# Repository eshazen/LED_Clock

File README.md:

# LED Clock

Yet another LED pseudo-analog clock.
<br>6 concentric circles of 60 LEDs plus one of 12 LEDs.
<br>Arduino Nano ESP32.

Current code (`clock_v3`) runs on 1Hz interrupts but expects
periodic time updates of the format `[hh:mm:ss]` at 1200 baud
from an external RTC.

First release code (`clock_v2`) just uses 1Hz timer interrupts
and provides hour / minute set buttons.

No ECOs on the PC board.  Forgot mounting holes though.
See `Case` folder for a two-part 3D printed wall hangar
with a little control panel for the set buttons.

Works OK but loses ~1min/day.  Need to work on the timekeeping.

### 2026-04-19

Implemented initial RTC board software.

### 2026-04-12

Working on SimpleRTC add-on to keep better time.
<br>Need a serial port on the ESP32.
<br>It's confusing:
https://forum.arduino.cc/t/nano-esp32-onboard-uart-and-pin-numbering-issues/1269099/9

I _think_ this should work:

    Serial1.begin(1200, SERIAL_8N1, D11, D12);

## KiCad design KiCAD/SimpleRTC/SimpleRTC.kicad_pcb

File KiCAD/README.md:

# PCB designs

`Led_clock_sector` is the main PCB.  No errors I'm aware of.
The current version here has mounting holes which are missing
from the V1 as-built version.

`SimpleRTC` is a small board with RTC, MCU and pushbuttons.
The version here in git as of this writing is incomplete...
no doubt there is an un-committed update on a laptop somewhere.

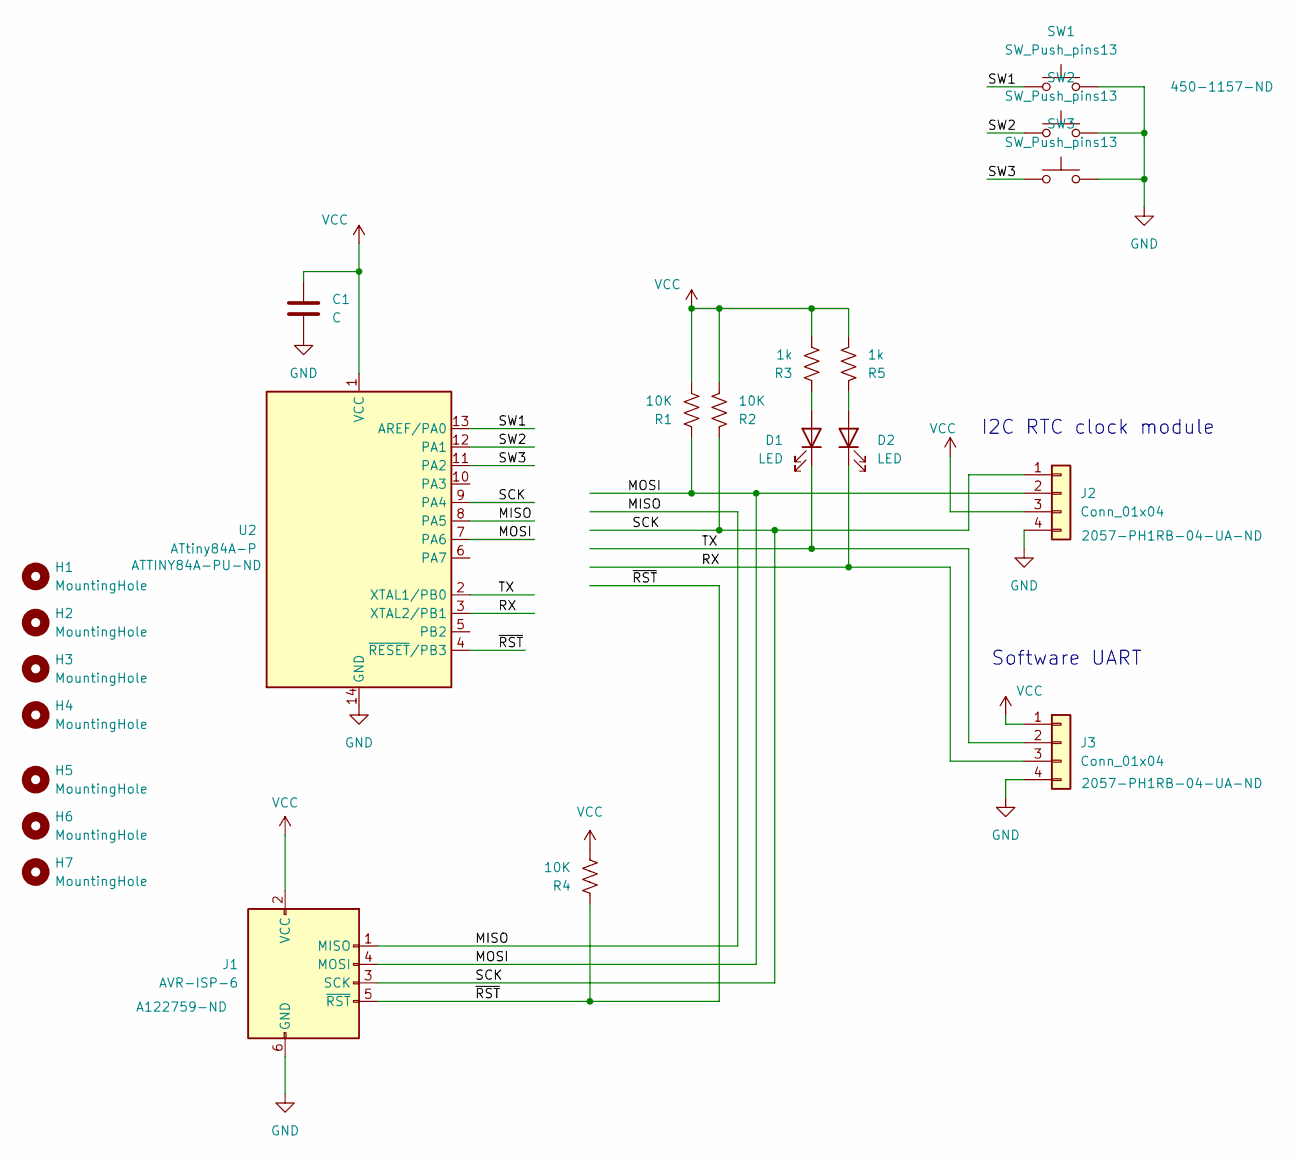
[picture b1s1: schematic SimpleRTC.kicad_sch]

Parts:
C1: C; C_1206_3216Metric_Pad1.33x1.80mm_HandSolder
D1, D2: LED; LED_1206_3216Metric_Pad1.42x1.75mm_HandSolder
H1, H2, H3, H4, H5, H6, H7: MountingHole; mtg_hole_256
J1: AVR-ISP-6; IDC-Header_2x03_P2.54mm_Vertical
J2: Conn_01x04; RTC_module
J3: Conn_01x04; PinHeader_1x04_P2.54mm_Horizontal
R1, R2, R4: 10K; R_1206_3216Metric_Pad1.30x1.75mm_HandSolder; DIGIKEY CF14JT10K0CT-ND
R3, R5: 1k; R_1206_3216Metric_Pad1.30x1.75mm_HandSolder; DIGIKEY CF14JT10K0CT-ND
SW1, SW2, SW3: SW_Push_pins13; SW_1437565-3
U2: ATtiny84A-P; DIP-14_W7.62mm

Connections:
/MISO: J1.1 (MISO), U2.8 (PA5)
/MOSI: J1.4 (MOSI), J2.2, R1.1, U2.7 (PA6)
/RX: D2.1 (K), J3.3, U2.3 (XTAL2/PB1)
/SCK: J1.3 (SCK), J2.1, R2.1, U2.9 (PA4)
/SW1: SW1.1, U2.13 (AREF/PA0)
/SW2: SW2.1, U2.12 (PA1)
/SW3: SW3.1, U2.11 (PA2)
/TX: D1.1 (K), J3.2, U2.2 (XTAL1/PB0)
/~RST: J1.5 (~RST), R4.1, U2.4 (~RESET/PB3)
GND: C1.2, J1.6 (GND), J2.4, J3.4, SW1.3, SW2.3, SW3.3, U2.14 (GND)
unnamed: D1.2 (A), R3.1
unnamed: D2.2 (A), R5.1
VCC: C1.1, J1.2 (VCC), J2.3, J3.1, R1.2, R2.2, R3.2, R4.2, R5.2, U2.1 (VCC)

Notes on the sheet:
I2C RTC clock module
Software UART

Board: 2 copper layers, 22 parts (14 on the bottom side), 13 nets, no tracks yet.

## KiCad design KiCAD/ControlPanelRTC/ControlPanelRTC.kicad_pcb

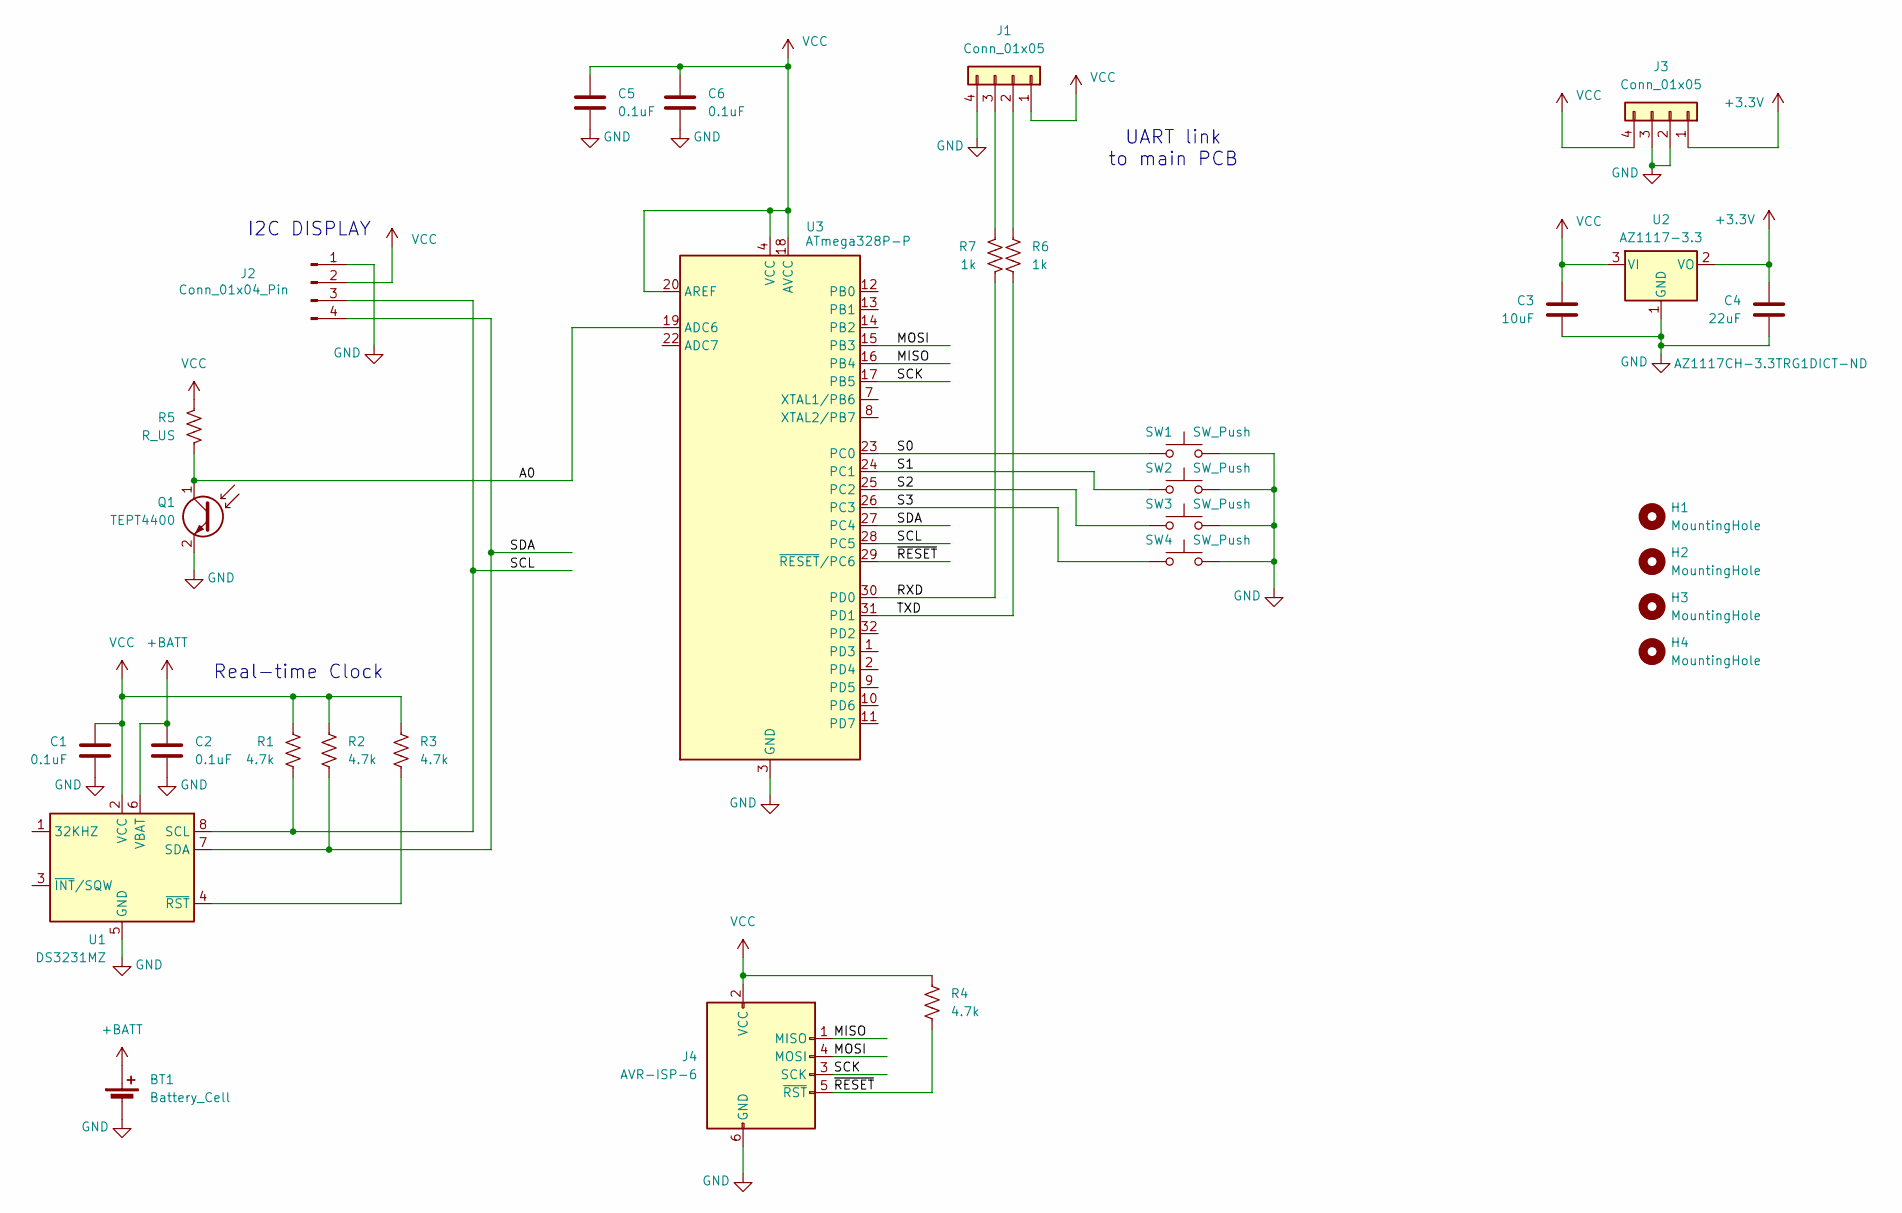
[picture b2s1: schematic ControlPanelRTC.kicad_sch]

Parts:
BT1: Battery_Cell; BatteryHolder_Keystone_3000_1x12mm
C1, C2, C5, C6: 0.1uF; C_1206_3216Metric_Pad1.33x1.80mm_HandSolder
C3: 10uF; C_1206_3216Metric_Pad1.33x1.80mm_HandSolder
C4: 22uF; C_1206_3216Metric_Pad1.33x1.80mm_HandSolder
H1, H2, H3, H4: MountingHole; mtg_440
J1, J3: Conn_01x05; PinHeader_1x04_P2.54mm_Horizontal
J2: Conn_01x04_Pin; OLED_0.96IN
J4: AVR-ISP-6; PinHeader_2x03_P2.54mm_Horizontal
Q1: TEPT4400; LED_D3.0mm_Clear
R1, R2, R3, R4: 4.7k; R_1206_3216Metric
R5: R_US; R_1206_3216Metric
R6, R7: 1k; R_1206_3216Metric
SW1, SW2, SW3, SW4: SW_Push; SW4_1825910-B_TEC
U1: DS3231MZ; SOIC-8_3.9x4.9mm_P1.27mm
U2: AZ1117-3.3; SOT-223-3_TabPin2
U3: ATmega328P-P; TQFP-32_7x7mm_P0.8mm

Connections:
+3.3V: C4.1, J3.1, U2.2 (VO)
+BATT: BT1.1 (+), C2.1, U1.6 (VBAT)
/A0: Q1.1 (C), R5.2, U3.19 (ADC6)
/MISO: J4.1 (MISO), U3.16 (PB4)
/MOSI: J4.4 (MOSI), U3.15 (PB3)
/RXD: R7.2, U3.30 (PD0)
/S0: SW1.1, U3.23 (PC0)
/S1: SW2.1, U3.24 (PC1)
/S2: SW3.1, U3.25 (PC2)
/S3: SW4.1, U3.26 (PC3)
/SCK: J4.3 (SCK), U3.17 (PB5)
/SCL: J2.3, R1.2, U1.8 (SCL), U3.28 (PC5)
/SDA: J2.4, R2.2, U1.7 (SDA), U3.27 (PC4)
/TXD: R6.2, U3.31 (PD1)
/~RESET: J4.5 (~RST), R4.2, U3.29 (~RESET/PC6)
GND: BT1.2 (-), C1.2, C2.2, C3.2, C4.2, C5.2, C6.2, J1.4, J2.1, J3.2, J3.3, J4.6 (GND), Q1.2 (E), SW1.3, SW2.3, SW3.3, SW4.3, U1.5 (GND), U2.1 (GND), U3.3 (GND), U3.5 (GND), U3.21 (GND)
unnamed: J1.2, R6.1
unnamed: J1.3, R7.1
unnamed: R3.2, U1.4 (~RST)
VCC: C1.1, C3.1, C5.1, C6.1, J1.1, J2.2, J3.4, J4.2 (VCC), R1.1, R2.1, R3.1, R4.1, R5.1, U1.2 (VCC), U2.3 (VI), U3.4 (VCC), U3.6 (VCC), U3.18 (AVCC), U3.20 (AREF)

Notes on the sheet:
UART link to main PCB
I2C DISPLAY
Real-time Clock

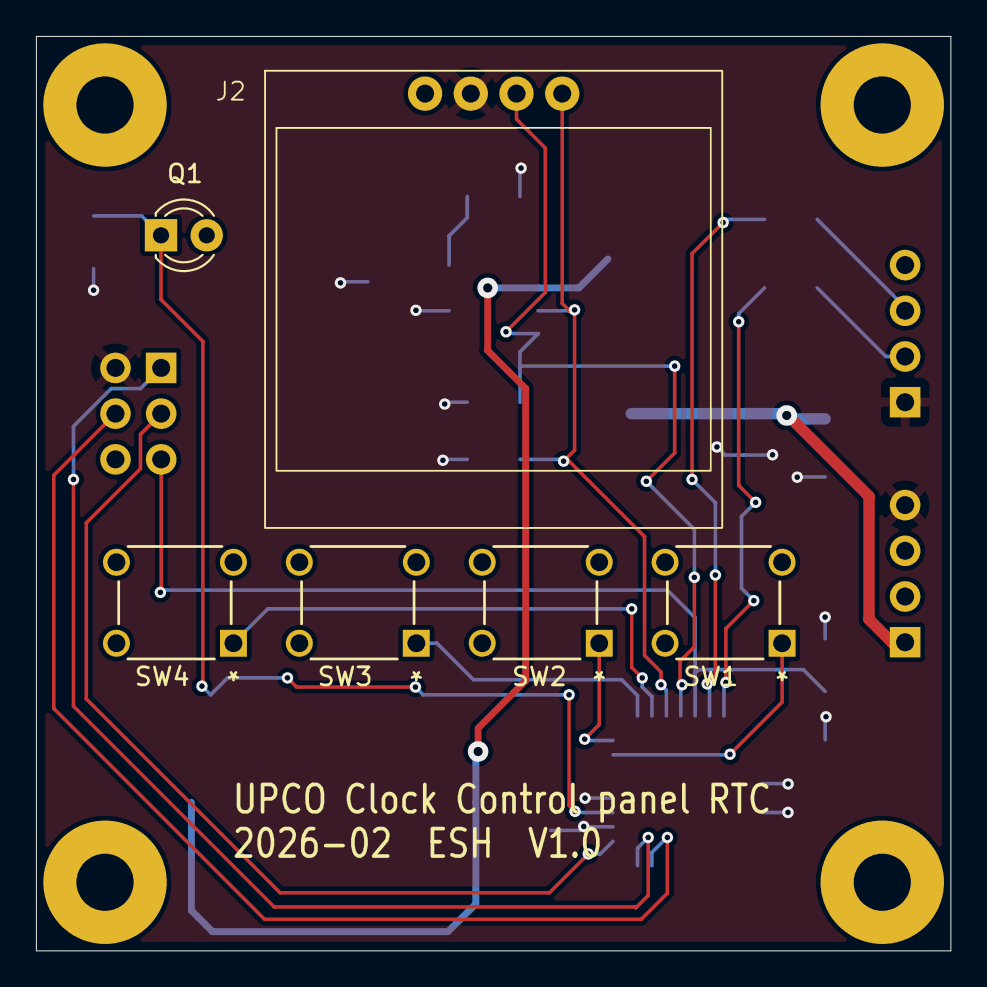
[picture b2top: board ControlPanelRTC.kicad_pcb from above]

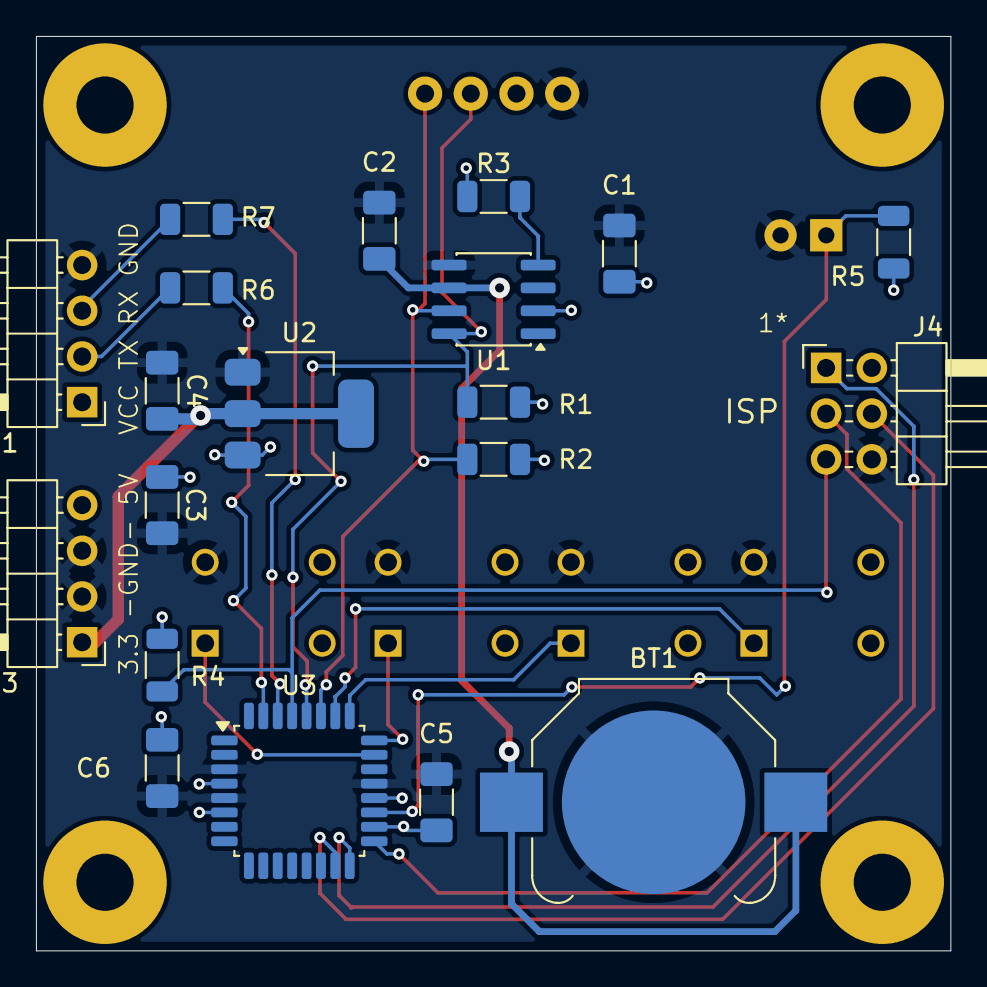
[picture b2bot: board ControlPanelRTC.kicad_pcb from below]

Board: 2 copper layers, 50.8 x 50.8 mm, 30 parts (20 on the bottom side), 20 nets.

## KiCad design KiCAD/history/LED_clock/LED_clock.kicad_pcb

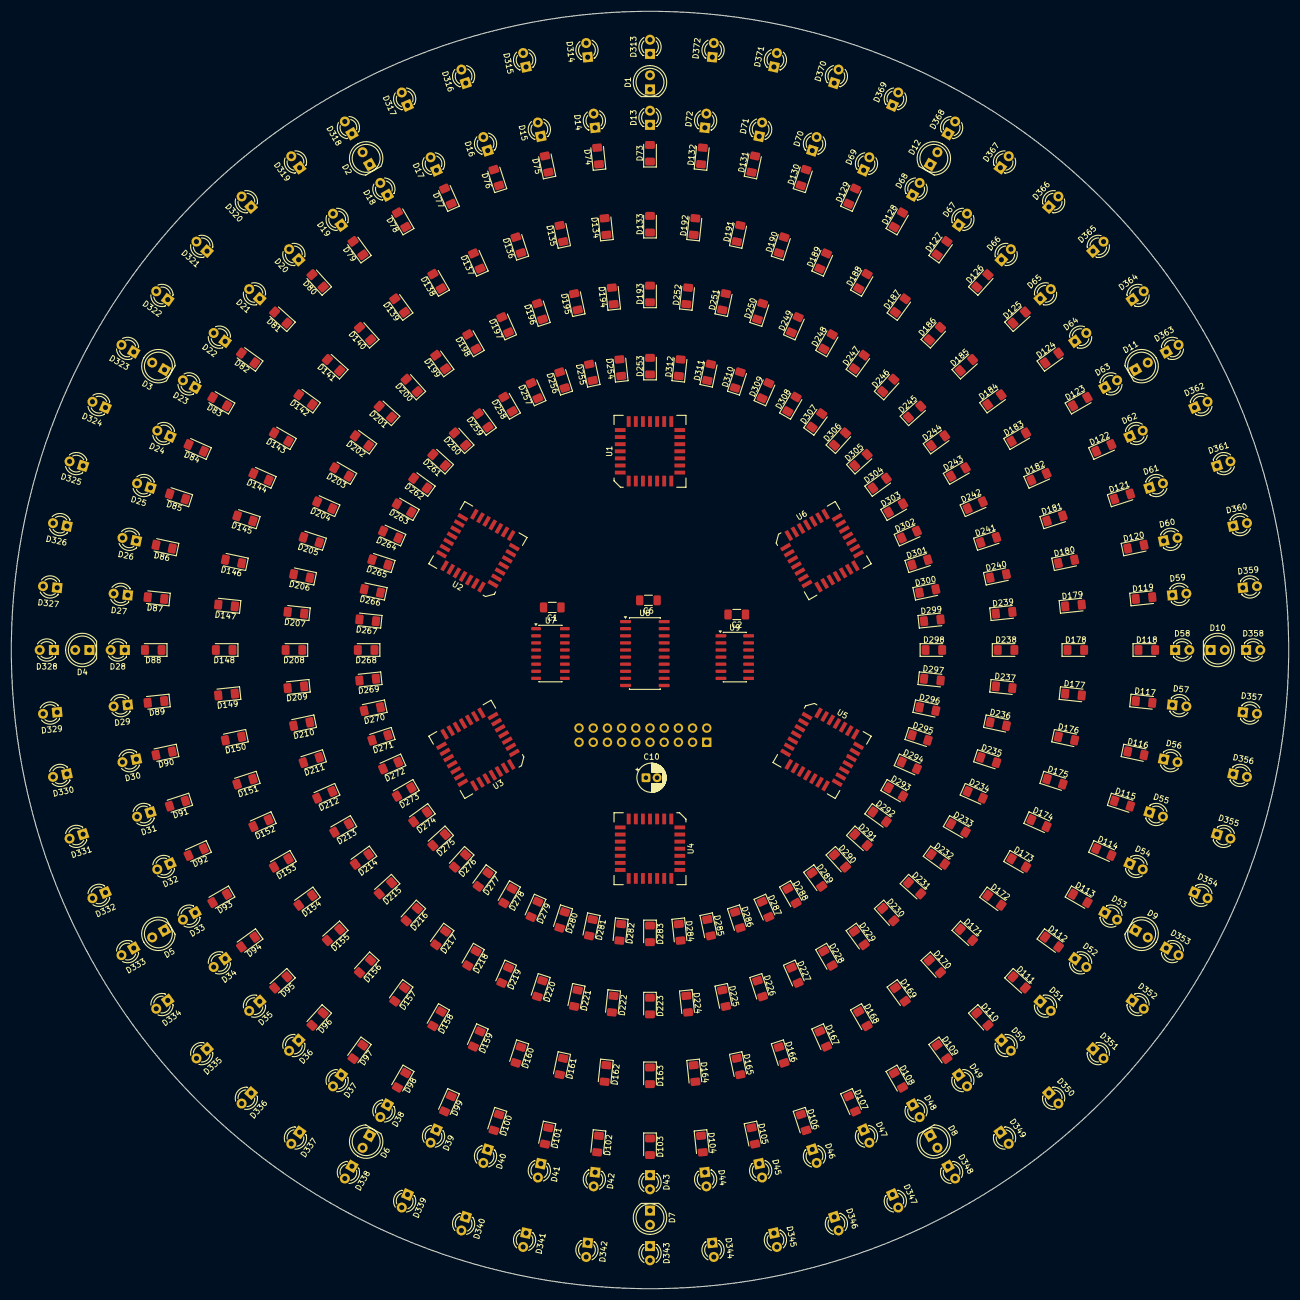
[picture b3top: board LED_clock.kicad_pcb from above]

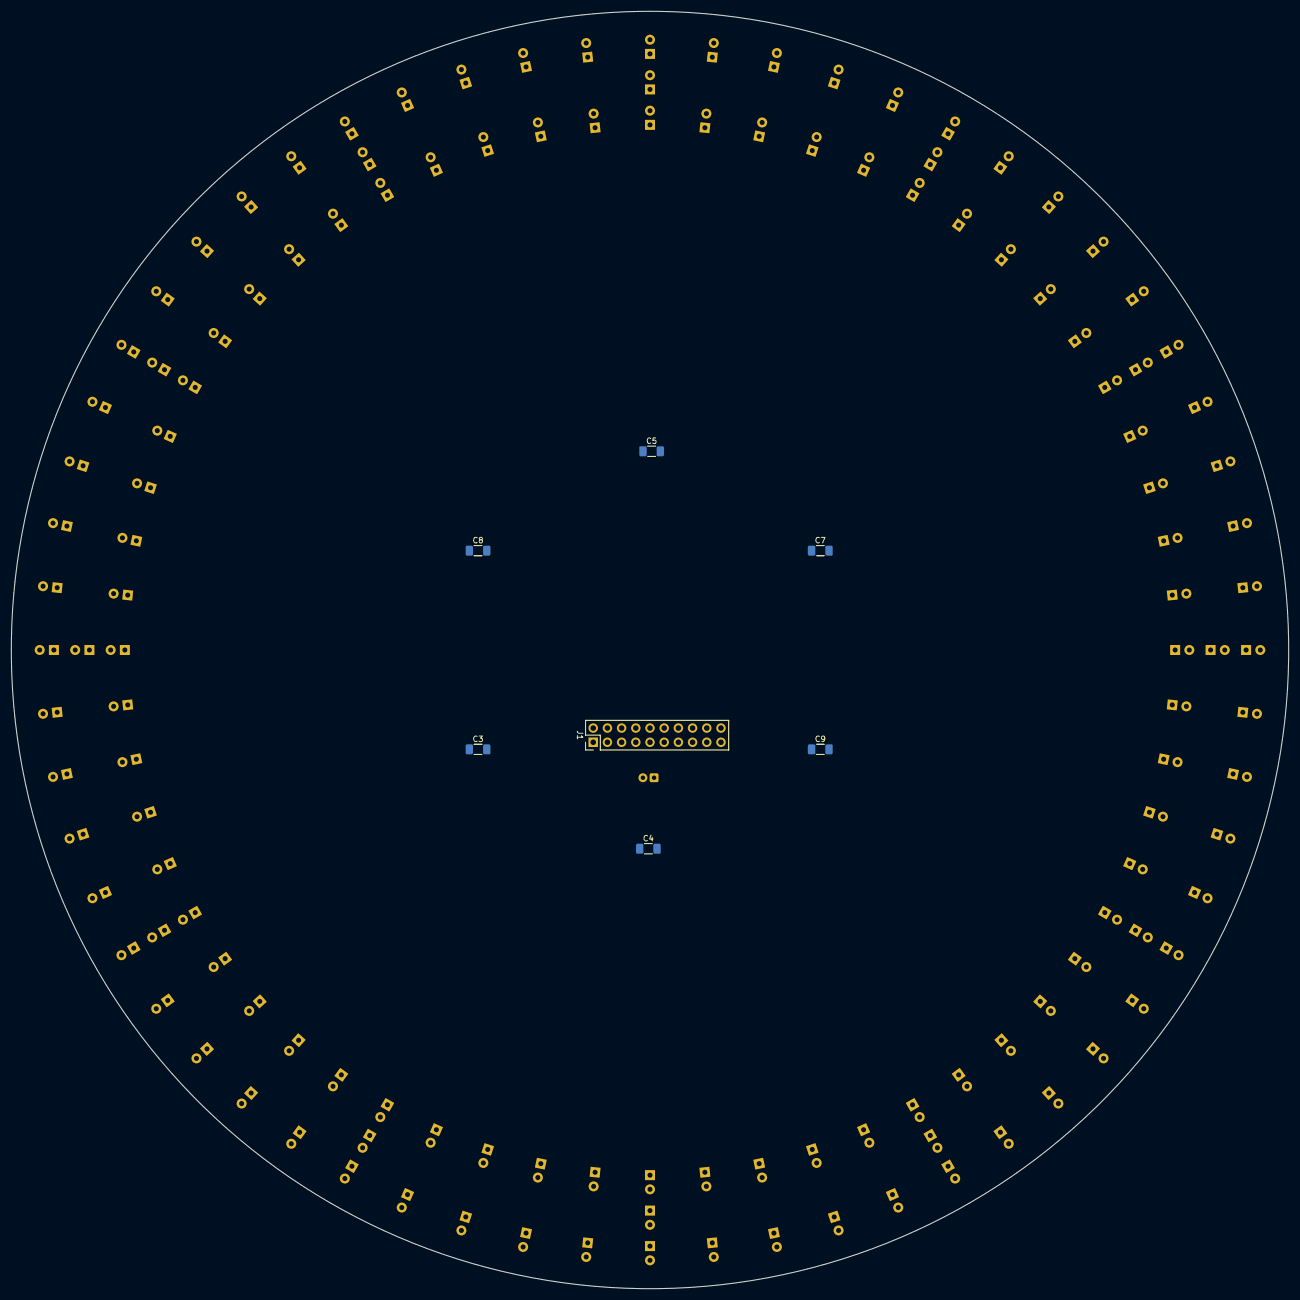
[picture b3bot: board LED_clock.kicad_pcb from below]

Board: 4 copper layers, 228.6 x 228.6 mm, 392 parts (7 on the bottom side), 121 nets, no tracks yet.

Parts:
C1, C2, C3, C4, C5, C6, C7, C8, C9: 0.1uF; C_1206_3216Metric_Pad1.33x1.80mm_HandSolder
C10: 33uF; CP_Radial_D5.0mm_P2.00mm
D1, D2, D3, D4, D5, D6, D7, D8, D9, D10, D11, D12: LED; LED_D5.0mm
D13, D14, D15, D16, D17, D18, D19, D20, D21, D22, D23, D24, D25, D26, D27, D28, D29, D30, D31, D32, D33, D34, D35, D36, D37, D38, D39, D40, D41, D42, D43, D44, D45, D46, D47, D48, D49, D50, D51, D52, D53, D54, D55, D56, D57, D58, D59, D60, D61, D62, D63, D64, D65, D66, D67, D68, D69, D70, D71, D72, D313, D314, D315, D316, D317, D318, D319, D320, D321, D322, D323, D324, D325, D326, D327, D328, D329, D330, D331, D332, D333, D334, D335, D336, D337, D338, D339, D340, D341, D342, D343, D344, D345, D346, D347, D348, D349, D350, D351, D352, D353, D354, D355, D356, D357, D358, D359, D360, D361, D362, D363, D364, D365, D366, D367, D368, D369, D370, D371, D372: LED; LED_D3.0mm
D73, D74, D75, D76, D77, D78, D79, D80, D81, D82, D83, D84, D85, D86, D87, D88, D89, D90, D91, D92, D93, D94, D95, D96, D97, D98, D99, D100, D101, D102, D103, D104, D105, D106, D107, D108, D109, D110, D111, D112, D113, D114, D115, D116, D117, D118, D119, D120, D121, D122, D123, D124, D125, D126, D127, D128, D129, D130, D131, D132, D133, D134, D135, D136, D137, D138, D139, D140, D141, D142, D143, D144, D145, D146, D147, D148, D149, D150, D151, D152, D153, D154, D155, D156, D157, D158, D159, D160, D161, D162, D163, D164, D165, D166, D167, D168, D169, D170, D171, D172, D173, D174, D175, D176, D177, D178, D179, D180, D181, D182, D183, D184, D185, D186, D187, D188, D189, D190, D191, D192, D193, D194, D195, D196, D197, D198, D199, D200, D201, D202, D203, D204, D205, D206, D207, D208, D209, D210, D211, D212, D213, D214, D215, D216, D217, D218, D219, D220, D221, D222, D223, D224, D225, D226, D227, D228, D229, D230, D231, D232, D233, D234, D235, D236, D237, D238, D239, D240, D241, D242, D243, D244, D245, D246, D247, D248, D249, D250, D251, D252, D253, D254, D255, D256, D257, D258, D259, D260, D261, D262, D263, D264, D265, D266, D267, D268, D269, D270, D271, D272, D273, D274, D275, D276, D277, D278, D279, D280, D281, D282, D283, D284, D285, D286, D287, D288, D289, D290, D291, D292, D293, D294, D295, D296, D297, D298, D299, D300, D301, D302, D303, D304, D305, D306, D307, D308, D309, D310, D311, D312: LED; LED_1206_3216Metric_Pad1.42x1.75mm_HandSolder
J1: CONN_2X10; PinHeader_2x10_P2.54mm_Vertical
U1, U2, U3, U4, U5, U6: ICM7218A; PLCC-28
U7: 74HC138; SO-16_3.9x9.9mm_P1.27mm
U8: 74LS244; SO-20_5.3x12.6mm_P1.27mm
U9: 74LS125; SO-14_3.9x8.65mm_P1.27mm

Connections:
/A0: J1.20, U7.1 (A0)
/A1: J1.19, U7.2 (A1)
/A2: J1.18, U7.3 (A2)
/D0: U1.12 (ID0), U2.12 (ID0), U3.12 (ID0), U4.12 (ID0), U5.12 (ID0), U6.12 (ID0), U8.18 (O0a)
/D1: U1.11 (ID1), U2.11 (ID1), U3.11 (ID1), U4.11 (ID1), U5.11 (ID1), U6.11 (ID1), U8.16 (O1a)
/D2: U1.13 (ID2), U2.13 (ID2), U3.13 (ID2), U4.13 (ID2), U5.13 (ID2), U6.13 (ID2), U8.14 (O2a)
/D3: U1.14 (ID3), U2.14 (ID3), U3.14 (ID3), U4.14 (ID3), U5.14 (ID3), U6.14 (ID3), U8.12 (O3a)
/D4: U1.10 (ID4), U2.10 (ID4), U3.10 (ID4), U4.10 (ID4), U5.10 (ID4), U6.10 (ID4), U8.9 (O0b)
/D5: U1.6 (ID5), U2.6 (ID5), U3.6 (ID5), U4.6 (ID5), U5.6 (ID5), U6.6 (ID5), U8.7 (O1b)
/D6: U1.5 (ID6), U2.5 (ID6), U3.5 (ID6), U4.5 (ID6), U5.5 (ID6), U6.5 (ID6), U8.5 (O2b)
/D7: U1.7 (ID7), U2.7 (ID7), U3.7 (ID7), U4.7 (ID7), U5.7 (ID7), U6.7 (ID7), U8.3 (O3b)
/MODE: U1.9 (MODE), U2.9 (MODE), U3.9 (MODE), U4.9 (MODE), U5.9 (MODE), U6.9 (MODE), U9.3
/R1_X0: D253.2 (A), D261.2 (A), D269.2 (A), D277.2 (A), D285.2 (A), D293.2 (A), D301.2 (A), D309.2 (A)
/R1_X1: D254.2 (A), D262.2 (A), D270.2 (A), D278.2 (A), D286.2 (A), D294.2 (A), D302.2 (A), D310.2 (A)
/R1_X2: D255.2 (A), D263.2 (A), D271.2 (A), D279.2 (A), D287.2 (A), D295.2 (A), D303.2 (A), D311.2 (A)
/R1_X3: D256.2 (A), D264.2 (A), D272.2 (A), D280.2 (A), D288.2 (A), D296.2 (A), D304.2 (A), D312.2 (A)
/R1_X4: D257.2 (A), D265.2 (A), D273.2 (A), D281.2 (A), D289.2 (A), D297.2 (A), D305.2 (A)
/R1_X5: D258.2 (A), D266.2 (A), D274.2 (A), D282.2 (A), D290.2 (A), D298.2 (A), D306.2 (A)
/R1_X6: D259.2 (A), D267.2 (A), D275.2 (A), D283.2 (A), D291.2 (A), D299.2 (A), D307.2 (A)
/R1_X7: D260.2 (A), D268.2 (A), D276.2 (A), D284.2 (A), D292.2 (A), D300.2 (A), D308.2 (A)
/R1_Y0: D253.1 (K), D254.1 (K), D255.1 (K), D256.1 (K), D257.1 (K), D258.1 (K), D259.1 (K), D260.1 (K)
/R1_Y1: D261.1 (K), D262.1 (K), D263.1 (K), D264.1 (K), D265.1 (K), D266.1 (K), D267.1 (K), D268.1 (K)
/R1_Y2: D269.1 (K), D270.1 (K), D271.1 (K), D272.1 (K), D273.1 (K), D274.1 (K), D275.1 (K), D276.1 (K)
/R1_Y3: D277.1 (K), D278.1 (K), D279.1 (K), D280.1 (K), D281.1 (K), D282.1 (K), D283.1 (K), D284.1 (K)
/R1_Y4: D285.1 (K), D286.1 (K), D287.1 (K), D288.1 (K), D289.1 (K), D290.1 (K), D291.1 (K), D292.1 (K)
/R1_Y5: D293.1 (K), D294.1 (K), D295.1 (K), D296.1 (K), D297.1 (K), D298.1 (K), D299.1 (K), D300.1 (K)
/R1_Y6: D301.1 (K), D302.1 (K), D303.1 (K), D304.1 (K), D305.1 (K), D306.1 (K), D307.1 (K), D308.1 (K)
/R1_Y7: D309.1 (K), D310.1 (K), D311.1 (K), D312.1 (K)
/R2_X0: D193.2 (A), D201.2 (A), D209.2 (A), D217.2 (A), D225.2 (A), D233.2 (A), D241.2 (A), D249.2 (A)
/R2_X1: D194.2 (A), D202.2 (A), D210.2 (A), D218.2 (A), D226.2 (A), D234.2 (A), D242.2 (A), D250.2 (A)
/R2_X2: D195.2 (A), D203.2 (A), D211.2 (A), D219.2 (A), D227.2 (A), D235.2 (A), D243.2 (A), D251.2 (A)
/R2_X3: D196.2 (A), D204.2 (A), D212.2 (A), D220.2 (A), D228.2 (A), D236.2 (A), D244.2 (A), D252.2 (A)
/R2_X4: D197.2 (A), D205.2 (A), D213.2 (A), D221.2 (A), D229.2 (A), D237.2 (A), D245.2 (A)
/R2_X5: D198.2 (A), D206.2 (A), D214.2 (A), D222.2 (A), D230.2 (A), D238.2 (A), D246.2 (A)
/R2_X6: D199.2 (A), D207.2 (A), D215.2 (A), D223.2 (A), D231.2 (A), D239.2 (A), D247.2 (A)
/R2_X7: D200.2 (A), D208.2 (A), D216.2 (A), D224.2 (A), D232.2 (A), D240.2 (A), D248.2 (A)
/R2_Y0: D193.1 (K), D194.1 (K), D195.1 (K), D196.1 (K), D197.1 (K), D198.1 (K), D199.1 (K), D200.1 (K)
/R2_Y1: D201.1 (K), D202.1 (K), D203.1 (K), D204.1 (K), D205.1 (K), D206.1 (K), D207.1 (K), D208.1 (K)
/R2_Y2: D209.1 (K), D210.1 (K), D211.1 (K), D212.1 (K), D213.1 (K), D214.1 (K), D215.1 (K), D216.1 (K)
/R2_Y3: D217.1 (K), D218.1 (K), D219.1 (K), D220.1 (K), D221.1 (K), D222.1 (K), D223.1 (K), D224.1 (K)
/R2_Y4: D225.1 (K), D226.1 (K), D227.1 (K), D228.1 (K), D229.1 (K), D230.1 (K), D231.1 (K), D232.1 (K)
/R2_Y5: D233.1 (K), D234.1 (K), D235.1 (K), D236.1 (K), D237.1 (K), D238.1 (K), D239.1 (K), D240.1 (K)
/R2_Y6: D241.1 (K), D242.1 (K), D243.1 (K), D244.1 (K), D245.1 (K), D246.1 (K), D247.1 (K), D248.1 (K)
/R2_Y7: D249.1 (K), D250.1 (K), D251.1 (K), D252.1 (K)
/R3_X0: D133.2 (A), D141.2 (A), D149.2 (A), D157.2 (A), D165.2 (A), D173.2 (A), D181.2 (A), D189.2 (A)
/R3_X1: D134.2 (A), D142.2 (A), D150.2 (A), D158.2 (A), D166.2 (A), D174.2 (A), D182.2 (A), D190.2 (A)
/R3_X2: D135.2 (A), D143.2 (A), D151.2 (A), D159.2 (A), D167.2 (A), D175.2 (A), D183.2 (A), D191.2 (A)
/R3_X3: D136.2 (A), D144.2 (A), D152.2 (A), D160.2 (A), D168.2 (A), D176.2 (A), D184.2 (A), D192.2 (A)
/R3_X4: D137.2 (A), D145.2 (A), D153.2 (A), D161.2 (A), D169.2 (A), D177.2 (A), D185.2 (A)
/R3_X5: D138.2 (A), D146.2 (A), D154.2 (A), D162.2 (A), D170.2 (A), D178.2 (A), D186.2 (A)
/R3_X6: D139.2 (A), D147.2 (A), D155.2 (A), D163.2 (A), D171.2 (A), D179.2 (A), D187.2 (A)
/R3_X7: D140.2 (A), D148.2 (A), D156.2 (A), D164.2 (A), D172.2 (A), D180.2 (A), D188.2 (A)
/R3_Y0: D133.1 (K), D134.1 (K), D135.1 (K), D136.1 (K), D137.1 (K), D138.1 (K), D139.1 (K), D140.1 (K)
/R3_Y1: D141.1 (K), D142.1 (K), D143.1 (K), D144.1 (K), D145.1 (K), D146.1 (K), D147.1 (K), D148.1 (K)
/R3_Y2: D149.1 (K), D150.1 (K), D151.1 (K), D152.1 (K), D153.1 (K), D154.1 (K), D155.1 (K), D156.1 (K)
/R3_Y3: D157.1 (K), D158.1 (K), D159.1 (K), D160.1 (K), D161.1 (K), D162.1 (K), D163.1 (K), D164.1 (K)
/R3_Y4: D165.1 (K), D166.1 (K), D167.1 (K), D168.1 (K), D169.1 (K), D170.1 (K), D171.1 (K), D172.1 (K)
/R3_Y5: D173.1 (K), D174.1 (K), D175.1 (K), D176.1 (K), D177.1 (K), D178.1 (K), D179.1 (K), D180.1 (K)
/R3_Y6: D181.1 (K), D182.1 (K), D183.1 (K), D184.1 (K), D185.1 (K), D186.1 (K), D187.1 (K), D188.1 (K)
/R3_Y7: D189.1 (K), D190.1 (K), D191.1 (K), D192.1 (K)
/R4_X0: D73.2 (A), D81.2 (A), D89.2 (A), D97.2 (A), D105.2 (A), D113.2 (A), D121.2 (A), D129.2 (A)
/R4_X1: D74.2 (A), D82.2 (A), D90.2 (A), D98.2 (A), D106.2 (A), D114.2 (A), D122.2 (A), D130.2 (A)
/R4_X2: D75.2 (A), D83.2 (A), D91.2 (A), D99.2 (A), D107.2 (A), D115.2 (A), D123.2 (A), D131.2 (A)
/R4_X3: D76.2 (A), D84.2 (A), D92.2 (A), D100.2 (A), D108.2 (A), D116.2 (A), D124.2 (A), D132.2 (A)
/R4_X4: D9.1 (K), D77.2 (A), D85.2 (A), D93.2 (A), D101.2 (A), D109.2 (A), D117.2 (A), D125.2 (A)
/R4_X5: D10.1 (K), D78.2 (A), D86.2 (A), D94.2 (A), D102.2 (A), D110.2 (A), D118.2 (A), D126.2 (A)
/R4_X6: D11.1 (K), D79.2 (A), D87.2 (A), D95.2 (A), D103.2 (A), D111.2 (A), D119.2 (A), D127.2 (A)
/R4_X7: D12.1 (K), D80.2 (A), D88.2 (A), D96.2 (A), D104.2 (A), D112.2 (A), D120.2 (A), D128.2 (A)
/R4_Y0: D73.1 (K), D74.1 (K), D75.1 (K), D76.1 (K), D77.1 (K), D78.1 (K), D79.1 (K), D80.1 (K)
/R4_Y1: D81.1 (K), D82.1 (K), D83.1 (K), D84.1 (K), D85.1 (K), D86.1 (K), D87.1 (K), D88.1 (K)
/R4_Y2: D89.1 (K), D90.1 (K), D91.1 (K), D92.1 (K), D93.1 (K), D94.1 (K), D95.1 (K), D96.1 (K)
/R4_Y3: D97.1 (K), D98.1 (K), D99.1 (K), D100.1 (K), D101.1 (K), D102.1 (K), D103.1 (K), D104.1 (K)
/R4_Y4: D105.1 (K), D106.1 (K), D107.1 (K), D108.1 (K), D109.1 (K), D110.1 (K), D111.1 (K), D112.1 (K)
/R4_Y5: D113.1 (K), D114.1 (K), D115.1 (K), D116.1 (K), D117.1 (K), D118.1 (K), D119.1 (K), D120.1 (K)
/R4_Y6: D9.2 (A), D10.2 (A), D11.2 (A), D12.2 (A), D121.1 (K), D122.1 (K), D123.1 (K), D124.1 (K), D125.1 (K), D126.1 (K), D127.1 (K), D128.1 (K)
/R4_Y7: D129.1 (K), D130.1 (K), D131.1 (K), D132.1 (K)
/R5_X0: D13.2 (A), D21.2 (A), D29.2 (A), D37.2 (A), D45.2 (A), D53.2 (A), D61.2 (A), D69.2 (A)
/R5_X1: D14.2 (A), D22.2 (A), D30.2 (A), D38.2 (A), D46.2 (A), D54.2 (A), D62.2 (A), D70.2 (A)
/R5_X2: D15.2 (A), D23.2 (A), D31.2 (A), D39.2 (A), D47.2 (A), D55.2 (A), D63.2 (A), D71.2 (A)
/R5_X3: D16.2 (A), D24.2 (A), D32.2 (A), D40.2 (A), D48.2 (A), D56.2 (A), D64.2 (A), D72.2 (A)
/R5_X4: D5.1 (K), D17.2 (A), D25.2 (A), D33.2 (A), D41.2 (A), D49.2 (A), D57.2 (A), D65.2 (A)
/R5_X5: D6.1 (K), D18.2 (A), D26.2 (A), D34.2 (A), D42.2 (A), D50.2 (A), D58.2 (A), D66.2 (A)
/R5_X6: D7.1 (K), D19.2 (A), D27.2 (A), D35.2 (A), D43.2 (A), D51.2 (A), D59.2 (A), D67.2 (A)
/R5_X7: D8.1 (K), D20.2 (A), D28.2 (A), D36.2 (A), D44.2 (A), D52.2 (A), D60.2 (A), D68.2 (A)
/R5_Y0: D13.1 (K), D14.1 (K), D15.1 (K), D16.1 (K), D17.1 (K), D18.1 (K), D19.1 (K), D20.1 (K)
/R5_Y1: D21.1 (K), D22.1 (K), D23.1 (K), D24.1 (K), D25.1 (K), D26.1 (K), D27.1 (K), D28.1 (K)
/R5_Y2: D29.1 (K), D30.1 (K), D31.1 (K), D32.1 (K), D33.1 (K), D34.1 (K), D35.1 (K), D36.1 (K)
/R5_Y3: D37.1 (K), D38.1 (K), D39.1 (K), D40.1 (K), D41.1 (K), D42.1 (K), D43.1 (K), D44.1 (K)
/R5_Y4: D45.1 (K), D46.1 (K), D47.1 (K), D48.1 (K), D49.1 (K), D50.1 (K), D51.1 (K), D52.1 (K)
/R5_Y5: D53.1 (K), D54.1 (K), D55.1 (K), D56.1 (K), D57.1 (K), D58.1 (K), D59.1 (K), D60.1 (K)
/R5_Y6: D5.2 (A), D6.2 (A), D7.2 (A), D8.2 (A), D61.1 (K), D62.1 (K), D63.1 (K), D64.1 (K), D65.1 (K), D66.1 (K), D67.1 (K), D68.1 (K)
/R5_Y7: D69.1 (K), D70.1 (K), D71.1 (K), D72.1 (K)
/R7_X0: D313.2 (A), D321.2 (A), D329.2 (A), D337.2 (A), D345.2 (A), D353.2 (A), D361.2 (A), D369.2 (A), U1.15 (d1), U2.15 (d1), U3.15 (d1), U4.15 (d1), U5.15 (d1), U6.15 (d1)
/R7_X1: D314.2 (A), D322.2 (A), D330.2 (A), D338.2 (A), D346.2 (A), D354.2 (A), D362.2 (A), D370.2 (A), U1.16 (d2), U2.16 (d2), U3.16 (d2), U4.16 (d2), U5.16 (d2), U6.16 (d2)
/R7_X2: D315.2 (A), D323.2 (A), D331.2 (A), D339.2 (A), D347.2 (A), D355.2 (A), D363.2 (A), D371.2 (A), U1.23 (d3), U2.23 (d3), U3.23 (d3), U4.23 (d3), U5.23 (d3), U6.23 (d3)
/R7_X3: D316.2 (A), D324.2 (A), D332.2 (A), D340.2 (A), D348.2 (A), D356.2 (A), D364.2 (A), D372.2 (A), U1.20 (d4), U2.20 (d4), U3.20 (d4), U4.20 (d4), U5.20 (d4), U6.20 (d4)
/R7_X4: D1.1 (K), D317.2 (A), D325.2 (A), D333.2 (A), D341.2 (A), D349.2 (A), D357.2 (A), D365.2 (A), U1.17 (d5), U2.17 (d5), U3.17 (d5), U4.17 (d5), U5.17 (d5), U6.17 (d5)
/R7_X5: D2.1 (K), D318.2 (A), D326.2 (A), D334.2 (A), D342.2 (A), D350.2 (A), D358.2 (A), D366.2 (A), U1.22 (d6), U2.22 (d6), U3.22 (d6), U4.22 (d6), U5.22 (d6), U6.22 (d6)
/R7_X6: D3.1 (K), D319.2 (A), D327.2 (A), D335.2 (A), D343.2 (A), D351.2 (A), D359.2 (A), D367.2 (A), U1.21 (d7), U2.21 (d7), U3.21 (d7), U4.21 (d7), U5.21 (d7), U6.21 (d7)
/R7_X7: D4.1 (K), D320.2 (A), D328.2 (A), D336.2 (A), D344.2 (A), D352.2 (A), D360.2 (A), D368.2 (A), U1.18 (d8), U2.18 (d8), U3.18 (d8), U4.18 (d8), U5.18 (d8), U6.18 (d8)
/R7_Y0: D313.1 (K), D314.1 (K), D315.1 (K), D316.1 (K), D317.1 (K), D318.1 (K), D319.1 (K), D320.1 (K), U1.27 (a), U2.27 (a), U3.27 (a), U4.27 (a), U5.27 (a), U6.27 (a)
/R7_Y1: D321.1 (K), D322.1 (K), D323.1 (K), D324.1 (K), D325.1 (K), D326.1 (K), D327.1 (K), D328.1 (K), U1.3 (b), U2.3 (b), U3.3 (b), U4.3 (b), U5.3 (b), U6.3 (b)
/R7_Y2: D329.1 (K), D330.1 (K), D331.1 (K), D332.1 (K), D333.1 (K), D334.1 (K), D335.1 (K), D336.1 (K), U1.1 (c), U2.1 (c), U3.1 (c), U4.1 (c), U5.1 (c), U6.1 (c)
/R7_Y3: D337.1 (K), D338.1 (K), D339.1 (K), D340.1 (K), D341.1 (K), D342.1 (K), D343.1 (K), D344.1 (K), U1.25 (d), U2.25 (d), U3.25 (d), U4.25 (d), U5.25 (d), U6.25 (d)
/R7_Y4: D345.1 (K), D346.1 (K), D347.1 (K), D348.1 (K), D349.1 (K), D350.1 (K), D351.1 (K), D352.1 (K), U1.2 (e), U2.2 (e), U3.2 (e), U4.2 (e), U5.2 (e), U6.2 (e)
/R7_Y5: D353.1 (K), D354.1 (K), D355.1 (K), D356.1 (K), D357.1 (K), D358.1 (K), D359.1 (K), D360.1 (K), U1.24 (f), U2.24 (f), U3.24 (f), U4.24 (f), U5.24 (f), U6.24 (f)
/R7_Y6: D1.2 (A), D2.2 (A), D3.2 (A), D4.2 (A), D361.1 (K), D362.1 (K), D363.1 (K), D364.1 (K), D365.1 (K), D366.1 (K), D367.1 (K), D368.1 (K), U1.26 (g), U2.26 (g), U3.26 (g), U4.26 (g), U5.26 (g), U6.26 (g)
/R7_Y7: D369.1 (K), D370.1 (K), D371.1 (K), D372.1 (K), U1.4 (dp), U2.4 (dp), U3.4 (dp), U4.4 (dp), U5.4 (dp), U6.4 (dp)
/~RING7: U1.8 (nWR), U2.8 (nWR), U3.8 (nWR), U4.8 (nWR), U5.8 (nWR), U6.8 (nWR), U7.10 (~Y5)
/~WR: J1.17, U7.4 (~E0)
GND: C1.2, C2.2, C3.2, C4.2, C5.2, C6.2, C7.2, C8.2, C9.2, C10.2, J1.4, J1.5, J1.10, J1.11, U1.28 (GND), U2.28 (GND), U3.28 (GND), U4.28 (GND), U5.28 (GND), U6.28 (GND), U7.5 (~E1), U7.8 (GND), U8.1 (OEa), U8.10 (GND), U8.19 (OEb), U9.1, U9.7 (GND)
unnamed: J1.6, U8.17 (I3b)
unnamed: J1.7, U8.15 (I2b)
unnamed: J1.8, U8.13 (I1b)
unnamed: J1.9, U8.11 (I0b)
unnamed: J1.12, U8.8 (I3a)
unnamed: J1.13, U8.6 (I2a)
unnamed: J1.14, U8.4 (I1a)
unnamed: J1.15, U8.2 (I0a)
unnamed: J1.16, U9.2
VCC: C1.1, C2.1, C3.1, C4.1, C5.1, C6.1, C7.1, C8.1, C9.1, C10.1, J1.1, J1.2, J1.3, U1.19 (V+), U2.19 (V+), U3.19 (V+), U4.19 (V+), U5.19 (V+), U6.19 (V+), U7.6 (E2), U7.16 (VCC), U8.20 (VCC), U9.14 (VCC)
